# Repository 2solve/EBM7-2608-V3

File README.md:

# IC2S EBM7-2608 V2.3 — variante fixa 4-20 mA

Placa de extensão da família IC2S (Extension Board Model 7) com **quatro entradas 4-20 mA**, **uma entrada de célula de
carga** e **um NTC de junta fria**, medidos por um ADC sigma-delta de 24 bits (**AD7124-8**). Encaixa por baixo na base board:
**P1** é o barramento (alimentação 24 V e 5 V, SPI do processador) e **P2** leva os sinais de campo.

Esta é a variante **fixa**: as quatro entradas são só 4-20 mA. A variante com selecção 0-10 V / 4-20 mA por MOSFET vive noutro
projecto (`EBM7-2608-V23_configuravel`).

Projecto KiCad 10 (testado em 10.0.5). Abrir
`Desenvolvimento_IC2S-EBM7-2608-V2.3-Fixo420/Projeto_IC2S-EBM7-2608-V2.3-Fixo420/IC2S-EBM7-2608-V2.3-Fixo420.kicad_pro`.

Identificador desta versão: **`IC2S-EBM7-2608-V2.3-Fixo420`** (produto IC2S-EBM7-2608, versão 2.3, variante fixa 4-20 mA).

---

## Estado (28-09-2026)

| Verificação | Resultado |
|---|---|
| DRC (`kicad-cli pcb drc --severity-all --schematic-parity`) | **0 erros**, 62 avisos (todos de serigrafia) |
| Ligações por fazer | 0 |
| Paridade esquemático ↔ PCB | 0 |
| ERC | 0 erros |

Não está pronta para fabricar: ver [Pendentes](#pendentes).

---

## Estrutura do repositório

Segue o padrão de pastas dos produtos da 2Solve (o mesmo de `Produtos/Axcel_Sensor`): uma pasta por versão, e dentro dela
projecto, documentos e ficheiros de fabricação, sempre com o identificador no nome.

```
Desenvolvimento_IC2S-EBM7-2608-V2.3-Fixo420/
├── Projeto_IC2S-EBM7-2608-V2.3-Fixo420/
│   ├── IC2S-EBM7-2608-V2.3-Fixo420.kicad_pro / .kicad_sch / .kicad_pcb / .kicad_dru
│   ├── 01_conectores … 08_ntc.kicad_sch          (as oito folhas)
│   ├── footprints/EBM7_V23.pretty, symbols/       (bibliotecas locais, por ${KIPRJMOD})
│   ├── Documentos_de_Referência-IC2S-EBM7-2608-V2.3-Fixo420/   (datasheets das peças desta placa)
│   └── Outputs/drc_report.json
├── Documentos_IC2S-EBM7-2608-V2.3-Fixo420/
│   ├── 00-Especificações_Técnicas_…/   verificações, relatórios, perguntas ao firmware
│   ├── 01-Esquemáticos_…/              Schematic-….pdf, ….step, …-Top_View.pdf, …-Bottom_View.pdf
│   ├── 02-Pinout_…/                    (vazio)
│   └── 03-Diagrama_Blocos_…/           (vazio)
└── Arquivos_Fabricação_IC2S-EBM7-2608-V2.3-Fixo420/
    ├── 00-Gerbers_…/                   ….GTL .G1 .G2 .GBL .GTS .GBS .GTO .GBO .Outline, ….TXT (furação), .gbrjob, .zip
    ├── 01-BOM_List_…/                  …-Preliminar.xlsx
    ├── 02-Pick-and-Place_…/            …-Pick-and-Place-Preliminar.csv
    └── 03-Stencil_…/                   ….GTP (pasta topo), ….GBP (pasta base)
```

Os ficheiros de fabricação e as vistas foram **gerados pelo `kicad-cli` a partir do projecto** a 28-09-2026 e são
**preliminares**: a placa ainda não passou a revisão independente do roteamento. Não enviar a fabricar sem essa revisão.

Os documentos em `00-Especificações_Técnicas` são registos da data em que foram escritos e citam os nomes antigos dos
ficheiros (`IC2S_Extension_Board_Model_7-EBM7-2608_V23L_Load_Cell_4AI.*`), anteriores à arrumação de 25-09-2026.

**Onde está cada decisão:** cada folha do esquemático tem um bloco de texto «DECISOES DESTA FOLHA» com notas numeradas. Neste
README cita-se sempre como *folha N, nota M*. A nota é a fonte; este documento resume.

---

## Como funciona, bloco a bloco

### Folha 1 — Conectores

- **P1** (Harwin M20-7822046, fila única de 20) liga à base board. Traz +24 V (P1.20), a massa GND_ADC (P1.19), +5 V, DGND e
  o SPI. Os pinos que esta placa não usa (USB, CS_DAC, I²C…) terminam aqui por desenho da família (nota 1).
- P1.20 leva ~116 mA em regime e ~180 mA em falha, 6 % do que o contacto aguenta (nota 2).
- **P2** (M20-7821446) é o conector de campo: excitação e sinais da célula, e os quatro laços (nota 5). Pinos 6-13 em pares
  `+24V_AINn` / `AINn`.

### Folha 2 — Entrada de 24 V e protecção

Caminho: P1.20 → TVS **D1** → fusível **F1** → díodo **D2** → **+24V_ADC**, que alimenta tudo: o conversor U1 e os laços.

- **F1 = Eaton CC12H750MA (time-lag)**: o I²t de fusão (150 mA²s) fica ~29× acima do arranque dos ~30 µF a jusante. O fusível anterior (FF,
  1,5 mA²s) abria no próprio arranque dos condensadores — um dos mecanismos da avaria em campo da V2.2 (notas 1, 2 e 10).
- **D1 = SMA6J33A-Q** (TVS de entrada): standoff 33 V, **clamp real 53,3 V** a 11,3 A — não os 40,6 V que dizia a biblioteca
  (nota 3).
- **C1 = 10 µF / 100 V em 1210**, condensador de entrada do U1: o datasheet da Recom (R-78HB-0.5, p.4) pede 3,3 µF / 100 V
  quando Vin pode passar de 50 V, e o clamp do TVS é 53,3 V (notas 4, 12 e 13).
- **Ramo único de 24 V** (28-09-2026, nota 13): F2, D3 e C2 saíram; o +24V_REG passou a ser o próprio +24V_ADC. Com
  116 mA em regime e ~180 mA em falha, F1 (750 mA) e D2 (1 A) chegam. Perde-se a selectividade: um curto no +24V_ADC
  abre F1 e desliga a placa inteira.
- **Condensadores** (nota 14): 100 nF de 50 V (TDK C1608X7R1H104K080AA) em todo o lado menos no C36, que está no
  +24V_ADC e fica a 100 V; 1 µF com um só MPN (TDK C1608X7R1H105K080AB).
- **Massas:** desde 24-09-2026 **GND_24V e GND_ADC são a mesma rede**. O net-tie que as unia (R1/R200) saiu (nota 7). Motivo:
  as duas são o mesmo domínio a montante; quem isola a lógica do processador é a MainBoard (conversor SCW12B-05), não esta placa.

### Folha 3 — Alimentação

Cadeia analógica: +24V_ADC → **U1** (Recom R-78HB5.0-0.5L, conversor 24→5 V) → FB1 → **+5V_ADC** → **U3** (SPX3819) → **+3.3V_ANA**.
A alimentação do lado do PLC (U2) está desenhada na folha 4, junto ao isolador que alimenta.

- O GND do U1 é GND_ADC: o +5V_ADC é a referência ratiométrica da célula (nota 2).
- O U1 não aceita ligação a quente (hot-plug) — aviso para o manual (nota 3).
- **Pré-carga do U1** (nota 13 e adenda de 15-09): o R-78HB só tem exactidão e regulação especificadas acima de ~10 % de carga;
  a placa sozinha fica em 1,6-6,8 %. Há posições para duas resistências de 220 R (0 / 22,7 / 45,5 mA); **a decisão faz-se na
  bancada**.
- **U4 = TL431B** grampeia o +3.3V_ANA a ~3,6 V (divisor 4k42 / 10k). É o sítio para onde os díodos de protecção das entradas
  despejam a corrente de um surto; sem ele o SPX3819, que só fornece corrente, deixava o rail subir até ~10 V e levava o ADC
  e a referência. Corrente real estimada 12-23 mA, contra 100 mA recomendados (nota 14, em que o componente aparece como U14).

### Folha 4 — Barreira digital

- **Alimentação do lado PLC:** +5 V do P1 → **U2** (SPX3819, o mesmo MPN do U3, desde 28-09; era MCP1824) → **+3.3V** (massa DGND), com C6/C8/C9 e os pontos de teste
  T3 (DGND) e T5 (+3.3V). Alimenta o lado 1 do isolador. Passou da folha 3 para esta em 25-09-2026, só no desenho
  (as ligações não mudaram); as notas que falam dela continuam na folha 3.
- **U5 = ISO7141** passa o SPI entre o lado do PLC (DGND) e o lado analógico (GND_ADC): 3 canais de ida (MOSI, CLK, CS) e 1 de
  volta (MISO), sempre habilitado (notas 3 e 4).
- **Não é isolamento de segurança nesta placa** (nota 1): os 2500 Vrms do ISO7141 exigiriam 3,7 mm de distância cobre-a-cobre e
  o PCB tem ~1 mm. Faz **separação de ruído** entre a lógica e a medida. Para um dia declarar isolamento: ≥ 3,7 mm ao longo da
  barreira (nota 5).
- **No PCB a barreira é física:** DGND e GND_ADC são zonas separadas nas camadas internas e em baixo. O `.kicad_dru` exige
  **1,0 mm** entre as redes do lado PLC (classe `DIGSIDE`) e o resto; há rule areas sem cobre debaixo do ISO7141
  (`keepout_barreira_ISO7141`) e junto ao P1 (`keepout_barreira_P1`, reposto a 25-09).
- Firmware: no arranque, reset do porto série do ADC (64 SCLK com DIN = 1), porque o CS pode oscilar na rampa de alimentação.

### Folha 5 — ADC

- **U6 = AD7124-8**, alimentado por +3.3V_ANA (AVDD, por um filtro passante NFM) e +3.3V_IOVDD (nota 4).
- **Referência dos laços: U7 = ADR4525 (2,5 V) no REFIN2**, por um único 0 Ω. Na V2.2 três 0 Ω punham 5 V nesse pino, acima do
  máximo absoluto de 3,6 V, em todas as placas (nota 1).
- **Célula ratiométrica no REFIN1** = metade da tensão de excitação (nota 2; folha 7, nota 10).
- SYNC com pull-up de 10k (o ADC não tem pull-up interno e com SYNC em baixo fica em reset) (nota 5).
- **Mapa de canais nesta placa:** AIN1 ← AIN4_ADC, AIN2 ← AIN3_ADC, AIN3 ← AIN2_ADC, AIN4 ← AIN1_ADC, AIN5/AIN6 = célula +/−,
  AIN8/AIN9 = NTC. O cruzamento dos laços é herdado da V2.2 e foi mantido para não trocar canais no firmware (folha 6, nota 4).
- Firmware (notas 8 e 9): REF_EN = 1; buffers de entrada ligados; REF_BUFP = REF_BUFM = 0 nos setups com REFIN2.
  As perguntas abertas ao firmware estão em `perguntas_firmware_EBM7_V23L_2026-09-24.md`.

### Folha 6 — Laços 4-20 mA (×4)

> **Rama `lacos-limitador-discreto` (02-10-2026):** os TPS26613 (U8-U11) e o TPS7A4001 (U12, +12V_TPS) foram substituídos
> por um limitador discreto por laço (BSP297 + BC847C + 18 Ω, porta num zener de 10 V). O que se descreve abaixo sobre o TPS
> vale para a `main`. Ver `00-Especificações_Técnicas…/alteracao_limitador_discreto_lacos_2026-10-02.md`.

Cada canal tem **dois caminhos** no P2, em pares de pinos:

- **Alimentação do sensor** (pino par, `+24V_AINn`): +24V_ADC → fusível **F3-F6** → borne, com o TVS **SMBJ36A** junto ao
  conector.
- **Sinal** (pino ímpar, `AINn`): borne → TVS **824500301** → protector **TPS26613** (U8-U11) → **burden 110 Ω 0,1 %** →
  ferrite → RC anti-aliasing → clamps **BAV199** para +3.3V_ANA → ADC.

- **Burden 110 Ω** (decisão de 21-09-2026, na caixa de texto da folha): 2,20 V a 20 mA, fim de escala do ADC (2,5 V) a 22,7 mA.
  Cumpre a nota (2) da Tabela 8-2 do TPS26613 (SLVSFE3C p.20): 4,46 V > 2,20 V. Os 409 Ω da V2.2 davam 8,18 V e violavam-na.
  **A constante do firmware muda de 6,25 para 9,09 mA/V.** MPN: Susumu RG1608P-111-B-T5.
- **TPS26613** limita a corrente a ~32 mA e desliga em sobretensão; aguenta um curto no cabo de campo (nota 8).
  O seu +Vs vem de **U12 = TPS7A4001** a 12 V, e não dos 24 V: o máximo de +Vs é 32 V e o TVS de entrada grampeia a 53,3 V
  (notas 9 e 16). Um só divisor VSNS para os quatro (nota 11).
- **F3-F6 = Schurter 3413.0006.22 (125 mA)** desde 25-09-2026 (nota 1). É **mitigação, não correcção**: aguenta o arranque de um
  sensor a 3 fios e surtos moderados, mas um surto forte ainda o abre. A correcção completa (díodo em série entre o fusível e o
  TVS) está só na variante configurável.
- **BAV199** em vez de BAT54S: fuga 5 nA em vez de 2 µA (nota 15).
- **U12 (TPS7A4001):** footprint corrigido a 25-09 para o land pattern da TI (SBVS162B p.22); os pads NC 3/6/7 ficam a 0,20 mm,
  com excepção própria no `.kicad_dru`. O condensador de entrada **C34 passou a 10 µF / 100 V em 1210**
  (GRM32EC72A106ME05L): o datasheet pede > 1 µF efectivo junto ao pino, e a 32 V um 0805 de 100 V dá ~0,64 µF.

### Folha 7 — Célula de carga

- **H1 (jumper 2×3)** escolhe a tensão de excitação: 1-2 = 2,5 V (U13, LDO), **3-4 = 5 V (omissão)**, 5-6 = 3,3 V (nota 15).
- Caminho: H1 → **D23** (Schottky RB162MM-60) → **R30 68 Ω 1 W** → P2.2 → ponte. O D23 impede que o clamp do campo volte
  para os rails; queda típica ~0,27 V a 11 mA e 25 °C (curva VF-IF do datasheet ROHM). O R30 passou a 1 W porque um curto de
  campo a 5 V dissipa 0,33 W (nota 16).
- TVS no campo (D8/D9 e D10), resistências de entrada 1k3 0,1 % e clamps BAV199 (notas 3, 4 e 12).
- **Medida ratiométrica:** REFIN1 = excitação/2 por um divisor 10k/10k casado; com REF_BUFP = 1 **sempre** (nota 10).
- Células aceites: 1-3 mV/V, 120-1000 Ω (nota 5).

### Folha 8 — NTC

- **Função:** compensação de **junta fria** para termopar; nunca usado em campo até hoje (nota 1).
- Divisor excitado pelo REFOUT do ADC, leitura diferencial em AIN8/AIN9 (notas 2 a 4). Com R21 = 22k a leitura fica dentro da
  gama dos buffers em −40…+85 °C (nota 7).

---

## Placa (PCB)

- 60 × 60 mm, 4 camadas. **F.Cu** sinal · **In1.Cu** e **In2.Cu** planos de massa partidos (DGND | GND_ADC), sem pistas ·
  **B.Cu** sinal e enchimento de massa.
- P1 e P2 montam em baixo (encaixe na base board).
- Classes de rede no `.kicad_pro`: Default, Analog, Digital, Loop, Power5, Power12, Power24 e `DIGSIDE` (auxiliar, só para a
  regra da barreira).

---

## Alterações de 24-28/09/2026

| Data | O quê | Porquê |
|---|---|---|
| 24-09 | GND_24V fundido em GND_ADC; R1 removido; D1 retorna a GND_ADC por via própria | mesmo domínio a montante |
| 25-09 | F3-F6 de 50 mA para 125 mA (3413.0006.22) | mitigar a abertura em surtos moderados e no arranque de sensores |
| 25-09 | Footprint do U12 (TPS7A4001) conforme SBVS162B p.22; regra dos pads NC | DRC limpo sem mentir sobre o land pattern |
| 25-09 | MPN dos burdens 110 Ω: RG1608P-111-B-T5 | faltava MPN |
| 25-09 | C34 → 10 µF / 100 V 1210 | CIN efectivo do TPS7A4001 |
| 25-09 | `keepout_barreira_P1` reposto | tinha desaparecido da placa |
| 25-09 | U2 (MCP1824) e C6/C8/C9/T3/T5 desenhados na folha 4 em vez da 3 | agrupar o lado PLC junto ao isolador; netlist igual |
| 28-09 | **Ramo único de 24 V**: saem F2, D3 e C2; F1 + D2 alimentam o U1 e o +24V_ADC; +24V_REG deixa de existir | reunião: é tudo alimentado pelos mesmos 24 V, não eram canais independentes nem isolados; ganha-se espaço |
| 28-09 | 100 nF fora do 24 V → TDK C1608X7R1H104K080AA (50 V), 24 peças; o C36 (+24V_ADC) fica GRM188R72A104KA35D (100 V) | 100 V estava sobredimensionado; pior caso fora do 24 V é o +12V_TPS a 31,7 V, por isso 50 V e não 25 V |
| 28-09 | 1 µF → TDK C1608X7R1H105K080AB (50 V) nos quatro | havia dois MPN para a mesma função |
| 28-09 | U2 MCP1824ST (SOT-223) → SPX3819 (SOT-23-5); **faltam rotear 6 ligações do U2** | mesmo MPN do U3; peça menor e mais barata (`alteracao_LDO_3V3_lado_PLC_2026-09-28.md`) |

---

## Notas do esquemático desactualizadas

Algumas notas foram escritas para outra revisão ou para a variante configurável e **não descrevem esta placa**. Até serem
corrigidas, vale o circuito:

- **Folha 5, nota 10** e **folha 6, notas 12-14** («MODO DUPLO», MOSFETs Q1-Q4, divisor 40k2/10k, 0-10 V): esta placa **não
  tem MOSFETs** nem selecção de modo. O mapa de canais correcto está na folha 5 acima.
- **Folha 6, caixa «DECISAO 21-09»**: fala em R10/R11/R12/R16 e R13/R14/R15/R17 — é a que vale para esta placa.
- **Referências de outras versões:** as notas dizem U3 = K78U05 (hoje **U1 = R-78HB5.0**), U14 = TL431 (hoje **U4**),
  U15 = TPS7A4001 (hoje **U12**), D200 = TVS de entrada (hoje **D1**), D31 = Schottky da excitação (hoje **D23**).
- **Folha 7, nota 11**: diz TPS7A2025 para o U13; a peça montada é o **LP5907MFX-2.5**.

---

## Documentos

Estão em `Desenvolvimento_…/Documentos_…/00-Especificações_Técnicas_IC2S-EBM7-2608-V2.3-Fixo420/`.

| Ficheiro | Conteúdo |
|---|---|
| `alteracoes_reuniao_2026-09-28.md` | revisão da reunião de 28-09: ramo único de 24 V, entrada do R-78HB, tensão dos 100 nF, MPN do 1 µF |
| `verificacao_aplicacao_TPS26613_V23L.md` | fórmulas e notas do datasheet do TPS26613 com os valores da BOM |
| `verificacao_aplicacao_AD7124_V23L_2026-09-24.md` | idem para o AD7124-8 (47 linhas avaliadas) |
| `verificacao_aplicacao_D14_pistas_V23L.md` | pistas debaixo do clamp D14 |
| `relatorio_roteamento_EBM7_V23L_2026-09-22.md` | revisão do roteamento a 22-09 |
| `relatorio_emc_EBM7_V23L_2026-09-23.md` | pré-conformidade EMC (CISPR 32 classe A) |
| `comparacao_BOM_V22_V23L_2026-09-23.md` | o que mudou na BOM desde a V2.2 fabricada |
| `perguntas_firmware_EBM7_V23L_2026-09-24.md` | perguntas abertas à equipa de firmware |
| `PROMPT_revisao_independente_V23L.md` | prompt para uma revisão independente em sessão nova |

---

## Pendentes

- **Rama `lacos-limitador-discreto`: o esquemático está à frente da PCB.**
  - Actualizar a PCB a partir do esquemático: entram Q1-Q8, R40-R48, D26 e C50; saem U8-U12, R22-R26, C26, C29, C31, C32,
    C37 e C38.
  - Trocar D6/D7/D8/D11 para DO-214AA e R13-R15/R17 para 1206.
  - **Dar a cada BSP297 (Q1-Q4) cobre para RthJA ≲ 90 K/W.**
  - Depois, ensaio de bancada da falha mantida a 32 V (ver o documento da alteração).
- **Rotear as ligações do U2 (SPX3819) e do C49 (2,2 µF na saída do U2)**, 28-09, e depois regenerar Gerbers, BOM, pick-and-place e stencil: os de 28-09 ainda mostram o MCP1824.
- Serigrafia: 62 avisos, legendas do H1, texto «5V» fora do contorno.
- Reescrever e assinar o requisito RF5 do escopo com a barreira real (DGND ↔ GND_ADC).
- Corrigir as notas desactualizadas listadas acima.
- Decidir a pré-carga do U1 na bancada.
- BOM final: a `…-Preliminar.xlsx` tem 55 linhas, 134 peças, 1 DNP (R8) e 133 a montar.
- Pick-and-place: o CSV tem 144 linhas, mais 11 do que as peças a montar — os 8 pontos de teste (T1-T8, `TestPad_Via`) e os
  3 fiduciais. Marcar esses footprints como «excluir dos ficheiros de posição» na placa antes de enviar à montadora.
- Datasheets que faltam em `Documentos_de_Referência`: SMBJ36A-13-F (Diodes), MBR1H100SFT3G (onsemi), BLM18PG471SN1D
  (Murata), LED KG EELP41.22 e as resistências genéricas (Yageo RC0603, Panasonic ERJ).
- Verificação do roteamento (`2shw-pcb:check-roteamento`) em **sessão independente**, antes de fabricar.
- O mecanismo da avaria em campo da V2.2 (família 2) **não foi medido** (medição G8 com osciloscópio). As protecções desta
  versão são correctas por si, mas não há prova de que resolvem essa avaria.

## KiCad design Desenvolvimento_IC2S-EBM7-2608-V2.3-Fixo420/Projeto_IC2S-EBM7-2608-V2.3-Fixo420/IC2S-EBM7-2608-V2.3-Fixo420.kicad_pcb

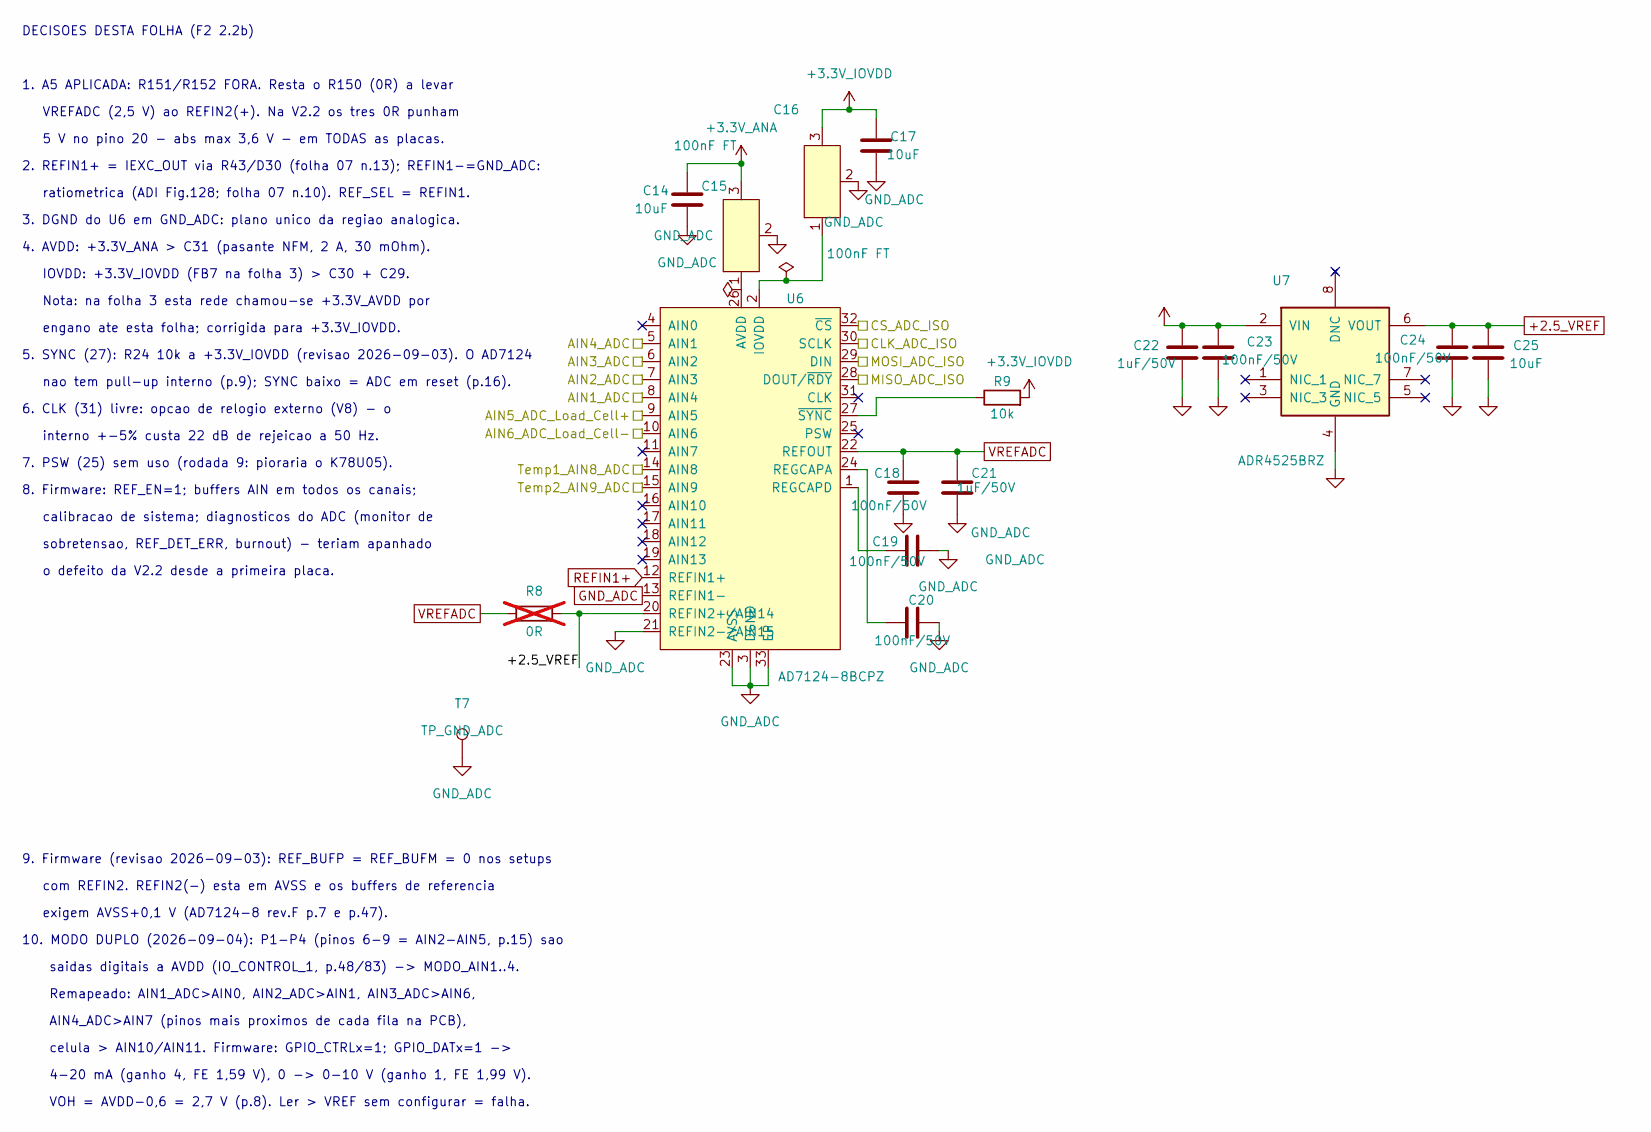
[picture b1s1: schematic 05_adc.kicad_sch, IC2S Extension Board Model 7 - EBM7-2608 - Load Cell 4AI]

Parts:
C14, C17, C25: 10uF; 0603C; MPN 0603YD106KAT2A
C15, C16: 100nF FT; NFM0603; MPN NFM18PC104R1C3D
C18, C19, C20, C23, C24: 100nF/50V; 0603C; MPN C1608X7R1H104K080AA
C21, C22: 1uF/50V; 0603C; MPN C1608X7R1H105K080AB
R8: 0R; 0603R; MPN RC0603JR-070RL; not fitted
R9: 10k; 0603R; MPN RC0603FR-0710KL
T7: TP_GND_ADC; TestPad_Via
U6: AD7124-8BCPZ; LFCSP-32-2; MPN AD7124-8BCPZ
U7: ADR4525BRZ; SOIC8; MPN ADR4525BRZ

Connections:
+2.5_VREF: C24.1, C25.1, R8.2, U6.20 (REFIN2+/AIN14), U7.6 (VOUT)
+3.3V_ANA: C14.2, C15.3 (OUT), C22.1, C23.1, U7.2 (VIN); also elsewhere on the board
+3.3V_IOVDD: C16.3 (OUT), C17.2, R9.2; also elsewhere on the board
/4 Barreira digital/CLK_ADC_ISO: U6.30 (SCLK); also elsewhere on the board
/4 Barreira digital/CS_ADC_ISO: U6.32 (~CS); also elsewhere on the board
/4 Barreira digital/MISO_ADC_ISO: U6.28 (DOUT/~RDY); also elsewhere on the board
/4 Barreira digital/MOSI_ADC_ISO: U6.29 (DIN); also elsewhere on the board
/5 ADC/AIN1_ADC: U6.8 (AIN4); also elsewhere on the board
/5 ADC/AIN2_ADC: U6.7 (AIN3); also elsewhere on the board
/5 ADC/AIN3_ADC: U6.6 (AIN2); also elsewhere on the board
/5 ADC/AIN4_ADC: U6.5 (AIN1); also elsewhere on the board
/5 ADC/AIN5_ADC_Load_Cell+: U6.9 (AIN5); also elsewhere on the board
/5 ADC/AIN6_ADC_Load_Cell-: U6.10 (AIN6); also elsewhere on the board
/5 ADC/Temp1_AIN8_ADC: U6.14 (AIN8); also elsewhere on the board
/5 ADC/Temp2_AIN9_ADC: U6.15 (AIN9); also elsewhere on the board
GND_ADC: C14.1, C15.2 (GND), C16.2 (GND), C17.1, C18.1, C19.1, C20.1, C21.2, C22.2, C23.2, C24.2, C25.2, T7.1 (1_1), U6.3 (DGND), U6.13 (REFIN1-), U6.21 (REFIN2-/AIN15), U6.23 (AVSS), U6.33 (EP), U7.4 (GND); also elsewhere on the board
unnamed: C15.1 (IN), U6.26 (AVDD)
unnamed: C16.1 (IN), U6.2 (IOVDD)
unnamed: C20.2, U6.24 (REGCAPA)
unnamed: C19.2, U6.1 (REGCAPD)
unnamed: R9.1, U6.27 (~SYNC)
REFIN1+: U6.12 (REFIN1+); also elsewhere on the board
VREFADC: C18.2, C21.1, R8.1, U6.22 (REFOUT); also elsewhere on the board

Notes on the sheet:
celula > AIN10/AIN11. Firmware: GPIO_CTRLx=1; GPIO_DATx=1 ->
ratiometrica (ADI Fig.128; folha 07 n.10). REF_SEL = REFIN1.
4. AVDD: +3.3V_ANA > C31 (pasante NFM, 2 A, 30 mOhm).
engano ate esta folha; corrigida para +3.3V_IOVDD.
Nota: na folha 3 esta rede chamou-se +3.3V_AVDD por
com REFIN2. REFIN2(-) esta em AVSS e os buffers de referencia
1. A5 APLICADA: R151/R152 FORA. Resta o R150 (0R) a levar
Remapeado: AIN1_ADC>AIN0, AIN2_ADC>AIN1, AIN3_ADC>AIN6,
calibracao de sistema; diagnosticos do ADC (monitor de
sobretensao, REF_DET_ERR, burnout) - teriam apanhado
saidas digitais a AVDD (IO_CONTROL_1, p.48/83) -> MODO_AIN1..4.
AIN4_ADC>AIN7 (pinos mais proximos de cada fila na PCB),
2. REFIN1+ = IEXC_OUT via R43/D30 (folha 07 n.13); REFIN1-=GND_ADC:
interno +-5% custa 22 dB de rejeicao a 50 Hz.
VREFADC (2,5 V) ao REFIN2(+). Na V2.2 os tres 0R punham
DECISOES DESTA FOLHA (F2 2.2b)
3. DGND do U6 em GND_ADC: plano unico da regiao analogica.
6. CLK (31) livre: opcao de relogio externo (V8) - o
10. MODO DUPLO (2026-09-04): P1-P4 (pinos 6-9 = AIN2-AIN5, p.15) sao
IOVDD: +3.3V_IOVDD (FB7 na folha 3) > C30 + C29.
o defeito da V2.2 desde a primeira placa.
nao tem pull-up interno (p.9); SYNC baixo = ADC em reset (p.16).
5. SYNC (27): R24 10k a +3.3V_IOVDD (revisao 2026-09-03). O AD7124
8. Firmware: REF_EN=1; buffers AIN em todos os canais;
VOH = AVDD-0,6 = 2,7 V (p.8). Ler > VREF sem configurar = falha.
7. PSW (25) sem uso (rodada 9: pioraria o K78U05).
5 V no pino 20 - abs max 3,6 V - em TODAS as placas.
exigem AVSS+0,1 V (AD7124-8 rev.F p.7 e p.47).
4-20 mA (ganho 4, FE 1,59 V), 0 -> 0-10 V (ganho 1, FE 1,99 V).
9. Firmware (revisao 2026-09-03): REF_BUFP = REF_BUFM = 0 nos setups

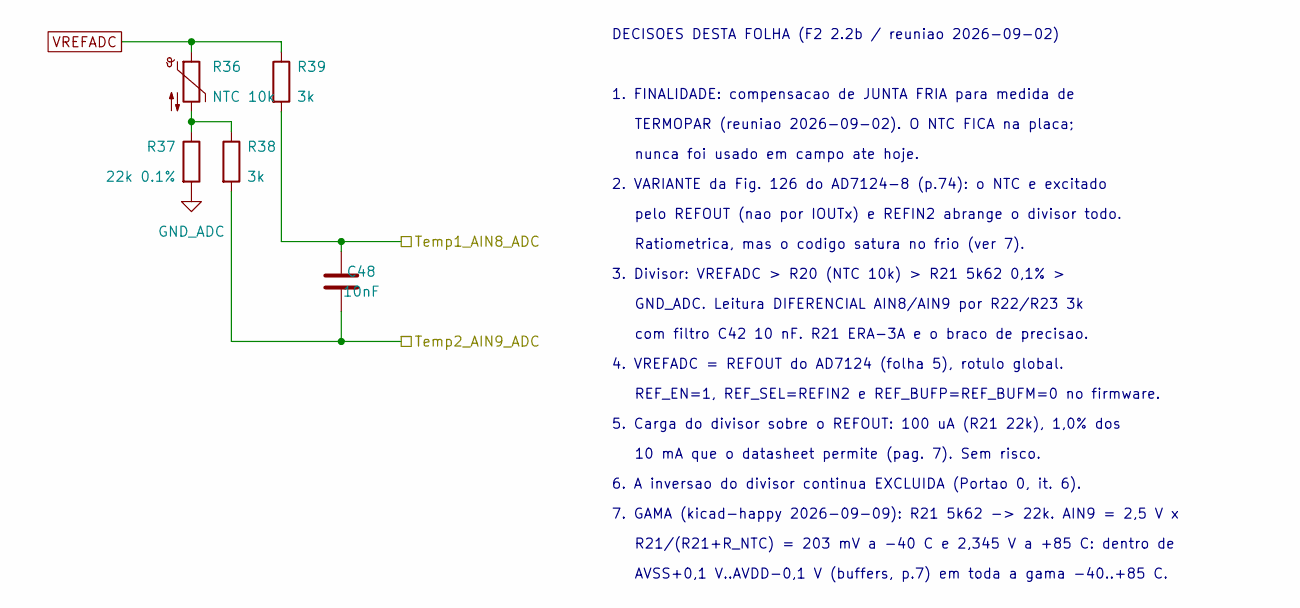
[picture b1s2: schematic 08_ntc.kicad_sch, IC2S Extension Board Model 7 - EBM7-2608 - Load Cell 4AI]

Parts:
C48: 10nF; 0603C; MPN GCM188R71H103KA37J
R36: NTC 10k; 0603R; MPN NTCS0603E3103JLT
R37: 22k 0.1%; 0603R; MPN RG1608P-223-B-T5
R38, R39: 3k; 0603R; MPN RC0603FR-073KL

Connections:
/5 ADC/Temp1_AIN8_ADC: C48.2, R39.2; also elsewhere on the board
/5 ADC/Temp2_AIN9_ADC: C48.1, R38.2; also elsewhere on the board
GND_ADC: R37.2; also elsewhere on the board
unnamed: R36.2, R37.1, R38.1
VREFADC: R36.1, R39.1; also elsewhere on the board

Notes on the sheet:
GND_ADC. Leitura DIFERENCIAL AIN8/AIN9 por R22/R23 3k
pelo REFOUT (nao por IOUTx) e REFIN2 abrange o divisor todo.
5. Carga do divisor sobre o REFOUT: 100 uA (R21 22k), 1,0% dos
Ratiometrica, mas o codigo satura no frio (ver 7).
4. VREFADC = REFOUT do AD7124 (folha 5), rotulo global.
nunca foi usado em campo ate hoje.
R21/(R21+R_NTC) = 203 mV a -40 C e 2,345 V a +85 C: dentro de
1. FINALIDADE: compensacao de JUNTA FRIA para medida de
2. VARIANTE da Fig. 126 do AD7124-8 (p.74): o NTC e excitado
REF_EN=1, REF_SEL=REFIN2 e REF_BUFP=REF_BUFM=0 no firmware.
10 mA que o datasheet permite (pag. 7). Sem risco.
3. Divisor: VREFADC > R20 (NTC 10k) > R21 5k62 0,1% >
DECISOES DESTA FOLHA (F2 2.2b / reuniao 2026-09-02)
6. A inversao do divisor continua EXCLUIDA (Portao 0, it. 6).
com filtro C42 10 nF. R21 ERA-3A e o braco de precisao.
TERMOPAR (reuniao 2026-09-02). O NTC FICA na placa;
7. GAMA (kicad-happy 2026-09-09): R21 5k62 -> 22k. AIN9 = 2,5 V x
AVSS+0,1 V..AVDD-0,1 V (buffers, p.7) em toda a gama -40..+85 C.

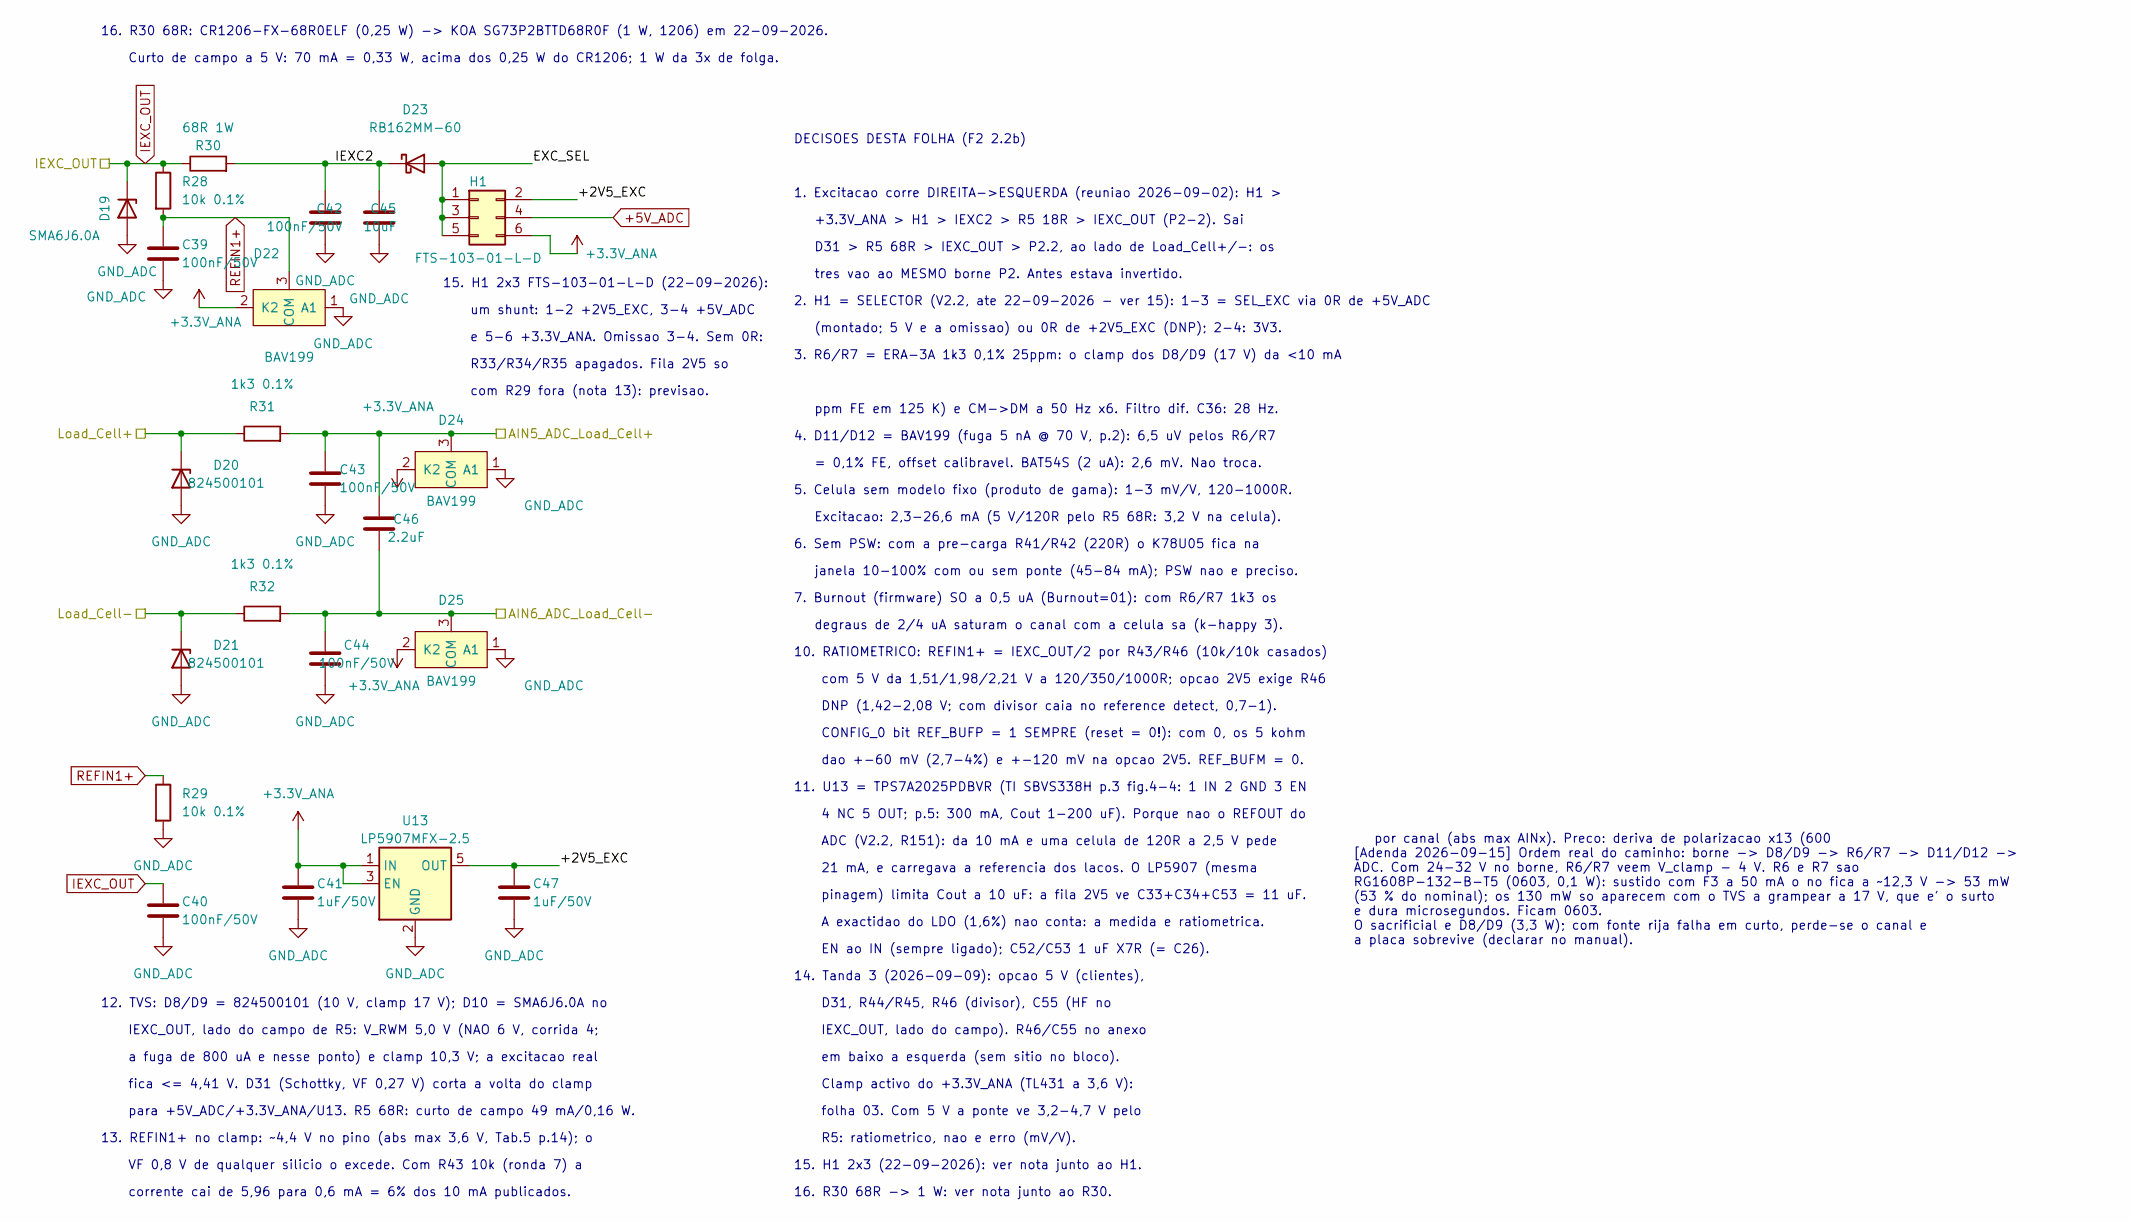
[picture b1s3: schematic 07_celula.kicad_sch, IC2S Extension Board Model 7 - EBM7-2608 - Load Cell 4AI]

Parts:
C39, C40, C42, C43, C44: 100nF/50V; 0603C; MPN C1608X7R1H104K080AA
C41, C47: 1uF/50V; 0603C; MPN C1608X7R1H105K080AB
C45: 10uF; 0603C; MPN 0603YD106KAT2A
C46: 2.2uF; 0603C; MPN C1608X5R1E225K080AB
D19: SMA6J6.0A; DO-214; MPN SMA6J6.0A
D20, D21: 824500101; DO-214; MPN 824500101
D22, D24, D25: BAV199; SOT23-3; MPN BAV199LT1G
D23: RB162MM-60; SOD-123F; MPN RB162MM-60TR
H1: FTS-103-01-L-D; HDR2X3_1.27mm-Without_number; MPN FTS-103-01-L-D
R28, R29: 10k 0.1%; 0603R; MPN RG1608P-103-B-T5
R30: 68R 1W; 1206R; MPN SG73P2BTTD68R0F
R31, R32: 1k3 0.1%; 0603R; MPN RG1608P-132-B-T5
U13: LP5907MFX-2.5; SOT-23-5; MPN LP5907MFX-2.5/NOPB

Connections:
+3.3V_ANA: C41.1, D22.2 (K2), D24.2 (K2), D25.2 (K2), H1.6, U13.1 (IN), U13.3 (EN); also elsewhere on the board
+5V_ADC: H1.4; also elsewhere on the board
/1 Conectores/Load_Cell+: D20.1 (K), R31.1; also elsewhere on the board
/1 Conectores/Load_Cell-: D21.1 (K), R32.1; also elsewhere on the board
/5 ADC/AIN5_ADC_Load_Cell+: C43.1, C46.2, D24.3 (COM), R31.2; also elsewhere on the board
/5 ADC/AIN6_ADC_Load_Cell-: C44.2, C46.1, D25.3 (COM), R32.2; also elsewhere on the board
/7 Celula de carga/+2V5_EXC: C47.1, H1.2, U13.5 (OUT)
/7 Celula de carga/EXC_SEL: D23.2 (A), H1.1, H1.3, H1.5
/7 Celula de carga/IEXC2: C42.2, C45.2, D23.1 (K), R30.2
GND_ADC: C39.2, C40.2, C41.2, C42.1, C43.2, C44.1, C45.1, C47.2, D19.2 (A), D20.2 (A), D21.2 (A), D22.1 (A1), D24.1 (A1), D25.1 (A1), R29.2, U13.2 (GND); also elsewhere on the board
IEXC_OUT: C40.1, D19.1 (K), R28.1, R30.1; also elsewhere on the board
REFIN1+: C39.1, D22.3 (COM), R28.2, R29.1; also elsewhere on the board

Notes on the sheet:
ADC (V2.2, R151): da 10 mA e uma celula de 120R a 2,5 V pede
14. Tanda 3 (2026-09-09): opcao 5 V (clientes),
folha 03. Com 5 V a ponte ve 3,2-4,7 V pelo
12. TVS: D8/D9 = 824500101 (10 V, clamp 17 V); D10 = SMA6J6.0A no
IEXC_OUT, lado do campo). R46/C55 no anexo
fica <= 4,41 V. D31 (Schottky, VF 0,27 V) corta a volta do clamp
dao +-60 mV (2,7-4%) e +-120 mV na opcao 2V5. REF_BUFM = 0.
a fuga de 800 uA e nesse ponto) e clamp 10,3 V; a excitacao real
Clamp activo do +3.3V_ANA (TL431 a 3,6 V):
15. H1 2x3 (22-09-2026): ver nota junto ao H1.
EN ao IN (sempre ligado); C52/C53 1 uF X7R (= C26).
13. REFIN1+ no clamp: ~4,4 V no pino (abs max 3,6 V, Tab.5 p.14); o
com 5 V da 1,51/1,98/2,21 V a 120/350/1000R; opcao 2V5 exige R46
corrente cai de 5,96 para 0,6 mA = 6% dos 10 mA publicados.
5. Celula sem modelo fixo (produto de gama): 1-3 mV/V, 120-1000R.
16. R30 68R: CR1206-FX-68R0ELF (0,25 W) -> KOA SG73P2BTTD68R0F (1 W, 1206) em 22-09-2026.
4. D11/D12 = BAV199 (fuga 5 nA @ 70 V, p.2): 6,5 uV pelos R6/R7
7. Burnout (firmware) SO a 0,5 uA (Burnout=01): com R6/R7 1k3 os
Curto de campo a 5 V: 70 mA = 0,33 W, acima dos 0,25 W do CR1206; 1 W da 3x de folga.
VF 0,8 V de qualquer silicio o excede. Com R43 10k (ronda 7) a
A exactidao do LDO (1,6%) nao conta: a medida e ratiometrica.
4 NC 5 OUT; p.5: 300 mA, Cout 1-200 uF). Porque nao o REFOUT do
3. R6/R7 = ERA-3A 1k3 0,1% 25ppm: o clamp dos D8/D9 (17 V) da <10 mA
16. R30 68R -> 1 W: ver nota junto ao R30.
em baixo a esquerda (sem sitio no bloco).
2. H1 = SELECTOR (V2.2, ate 22-09-2026 - ver 15): 1-3 = SEL_EXC via 0R de +5V_ADC
um shunt: 1-2 +2V5_EXC, 3-4 +5V_ADC
degraus de 2/4 uA saturam o canal com a celula sa (k-happy 3).
CONFIG_0 bit REF_BUFP = 1 SEMPRE (reset = 0!): com 0, os 5 kohm
Excitacao: 2,3-26,6 mA (5 V/120R pelo R5 68R: 3,2 V na celula).
para +5V_ADC/+3.3V_ANA/U13. R5 68R: curto de campo 49 mA/0,16 W.
IEXC_OUT, lado do campo de R5: V_RWM 5,0 V (NAO 6 V, corrida 4;
R5: ratiometrico, nao e erro (mV/V).
1. Excitacao corre DIREITA->ESQUERDA (reuniao 2026-09-02): H1 >
D31 > R5 68R > IEXC_OUT > P2.2, ao lado de Load_Cell+/-: os
R33/R34/R35 apagados. Fila 2V5 so
DNP (1,42-2,08 V; com divisor caia no reference detect, 0,7-1).
+3.3V_ANA > H1 > IEXC2 > R5 18R > IEXC_OUT (P2-2). Sai
ppm FE em 125 K) e CM->DM a 50 Hz x6. Filtro dif. C36: 28 Hz.
por canal (abs max AINx). Preco: deriva de polarizacao x13 (600 [Adenda 2026-09-15] Ordem real do caminho: borne -> D8/D9 -> R6/R7 -> D11/D12 -> ADC. Com 24-32 V no borne, R6/R7 veem V_clamp - 4 V. R6 e R7 sao RG1608P-132-B-T5 (0603, 0,1 W): sustido com F3 a 50 mA o no fica a ~12,3 V -> 53 mW (53 %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

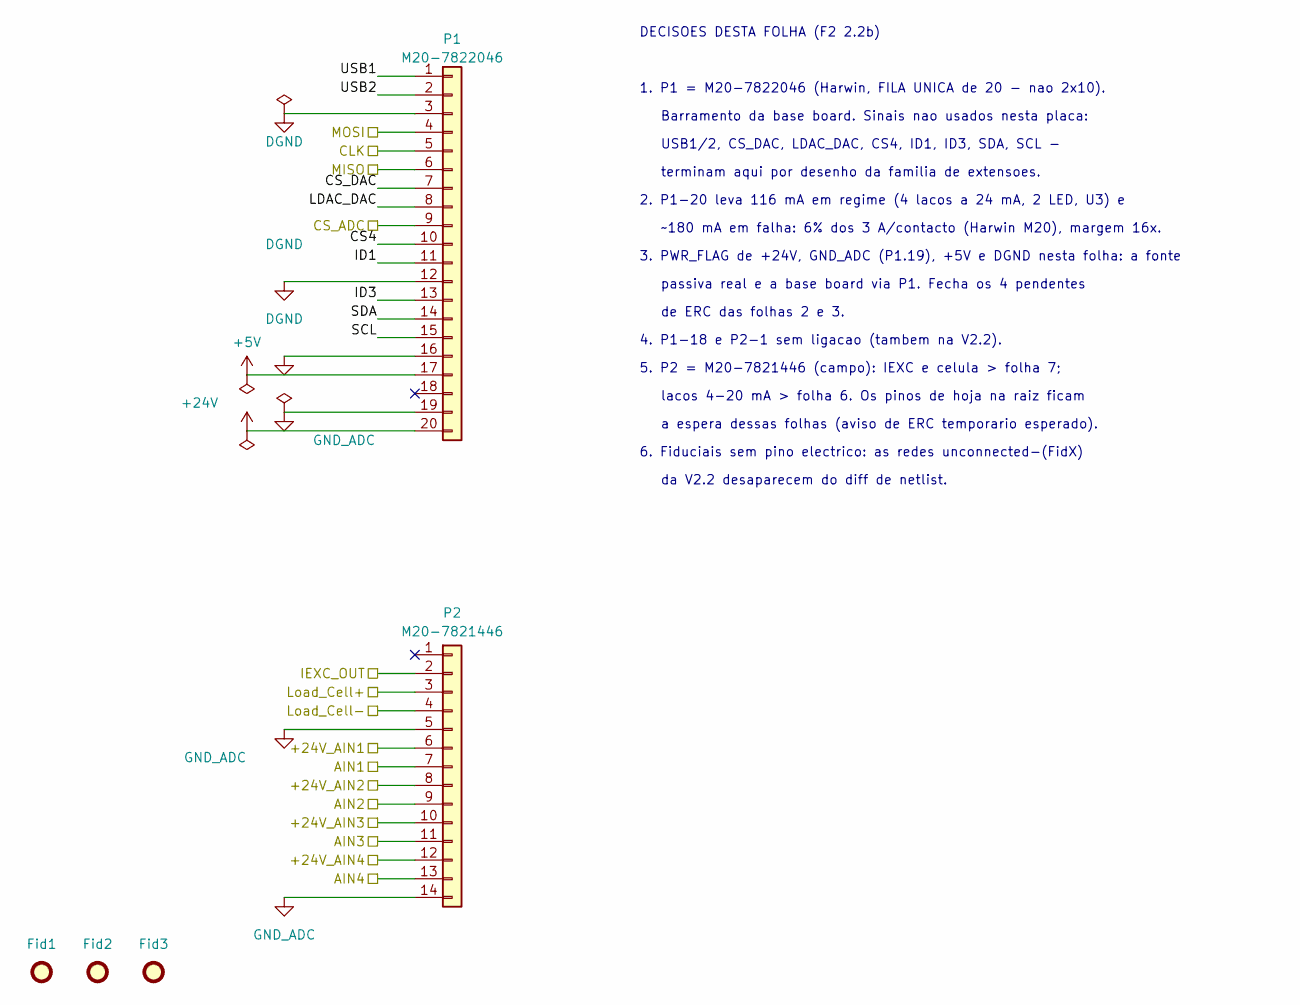
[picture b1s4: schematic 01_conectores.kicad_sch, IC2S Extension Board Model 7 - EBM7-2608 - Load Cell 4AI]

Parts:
Fid1, Fid2, Fid3: Fiducial; Fiducial_Point_Top-Bot
P1: M20-7822046; HDR1X20_FEMALE; MPN M20-7822046
P2: M20-7821446; HDR1X14_FEMALE; MPN M20-7821446

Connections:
+5V: P1.17; also elsewhere on the board
+24V: P1.20; also elsewhere on the board
/1 Conectores/+24V_AIN1: P2.6; also elsewhere on the board
/1 Conectores/+24V_AIN2: P2.8; also elsewhere on the board
/1 Conectores/+24V_AIN3: P2.10; also elsewhere on the board
/1 Conectores/+24V_AIN4: P2.12; also elsewhere on the board
/1 Conectores/AIN1: P2.7; also elsewhere on the board
/1 Conectores/AIN2: P2.9; also elsewhere on the board
/1 Conectores/AIN3: P2.11; also elsewhere on the board
/1 Conectores/AIN4: P2.13; also elsewhere on the board
/1 Conectores/CS4: P1.10
/1 Conectores/CS_DAC: P1.7
/1 Conectores/ID1: P1.11
/1 Conectores/ID3: P1.13
/1 Conectores/LDAC_DAC: P1.8
/1 Conectores/Load_Cell+: P2.3; also elsewhere on the board
/1 Conectores/Load_Cell-: P2.4; also elsewhere on the board
/1 Conectores/SCL: P1.15
/1 Conectores/SDA: P1.14
/1 Conectores/USB1: P1.1
/1 Conectores/USB2: P1.2
/CLK: P1.5; also elsewhere on the board
/CS_ADC: P1.9; also elsewhere on the board
/MISO: P1.6; also elsewhere on the board
/MOSI: P1.4; also elsewhere on the board
DGND: P1.3, P1.12, P1.16; also elsewhere on the board
GND_ADC: P1.19, P2.5, P2.14; also elsewhere on the board
IEXC_OUT: P2.2; also elsewhere on the board

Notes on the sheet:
de ERC das folhas 2 e 3.
Barramento da base board. Sinais nao usados nesta placa:
4. P1-18 e P2-1 sem ligacao (tambem na V2.2).
lacos 4-20 mA > folha 6. Os pinos de hoja na raiz ficam
~180 mA em falha: 6% dos 3 A/contacto (Harwin M20), margem 16x.
USB1/2, CS_DAC, LDAC_DAC, CS4, ID1, ID3, SDA, SCL -
6. Fiduciais sem pino electrico: as redes unconnected-(FidX)
5. P2 = M20-7821446 (campo): IEXC e celula > folha 7;
1. P1 = M20-7822046 (Harwin, FILA UNICA de 20 - nao 2x10).
2. P1-20 leva 116 mA em regime (4 lacos a 24 mA, 2 LED, U3) e
da V2.2 desaparecem do diff de netlist.
DECISOES DESTA FOLHA (F2 2.2b)
passiva real e a base board via P1. Fecha os 4 pendentes
3. PWR_FLAG de +24V, GND_ADC (P1.19), +5V e DGND nesta folha: a fonte
terminam aqui por desenho da familia de extensoes.
a espera dessas folhas (aviso de ERC temporario esperado).
